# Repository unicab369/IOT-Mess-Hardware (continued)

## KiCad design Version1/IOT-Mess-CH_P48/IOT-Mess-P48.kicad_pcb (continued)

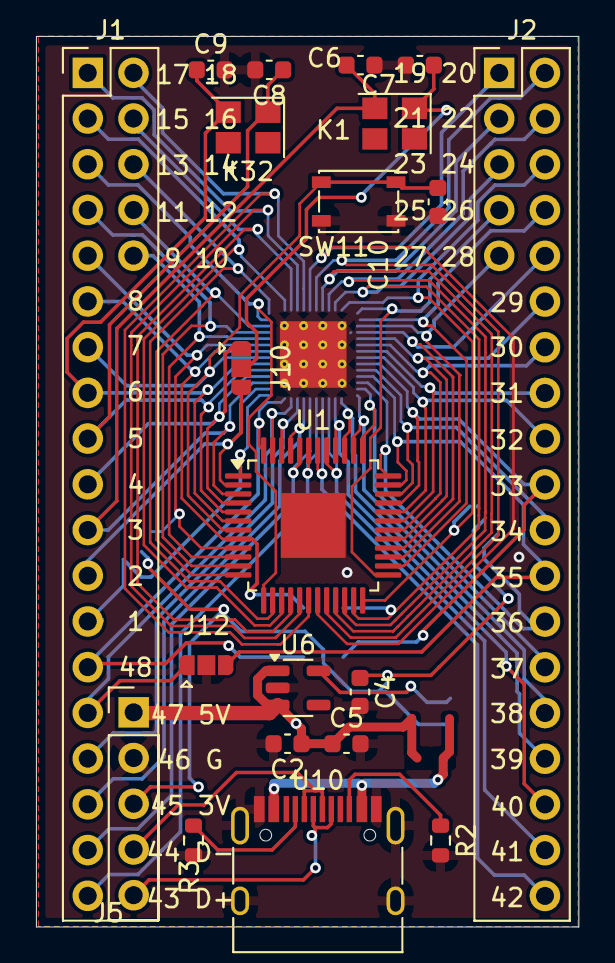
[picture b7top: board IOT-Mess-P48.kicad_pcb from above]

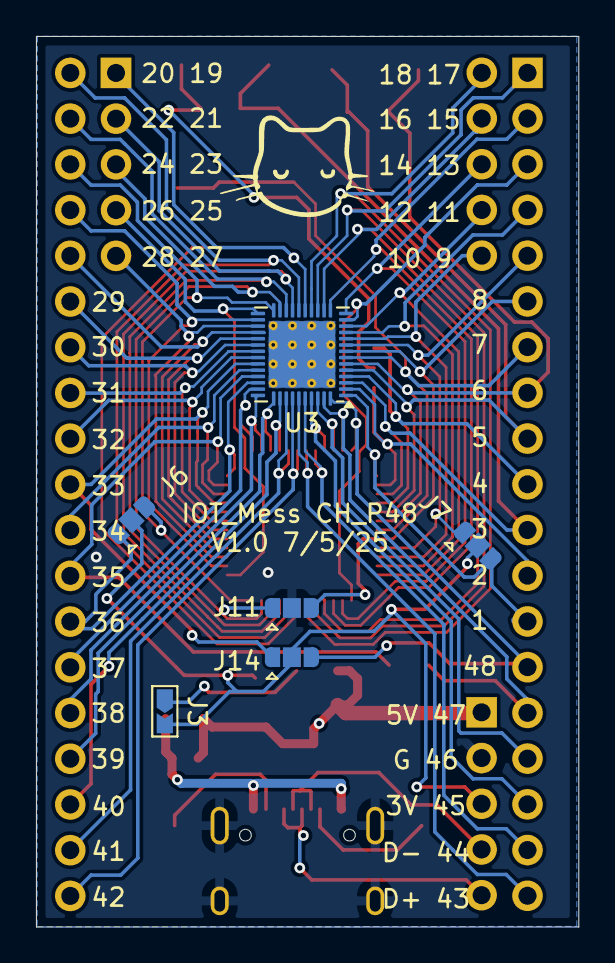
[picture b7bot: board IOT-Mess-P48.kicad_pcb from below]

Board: 2 copper layers, 30.1 x 49.5 mm, 27 parts (6 on the bottom side), 57 nets.

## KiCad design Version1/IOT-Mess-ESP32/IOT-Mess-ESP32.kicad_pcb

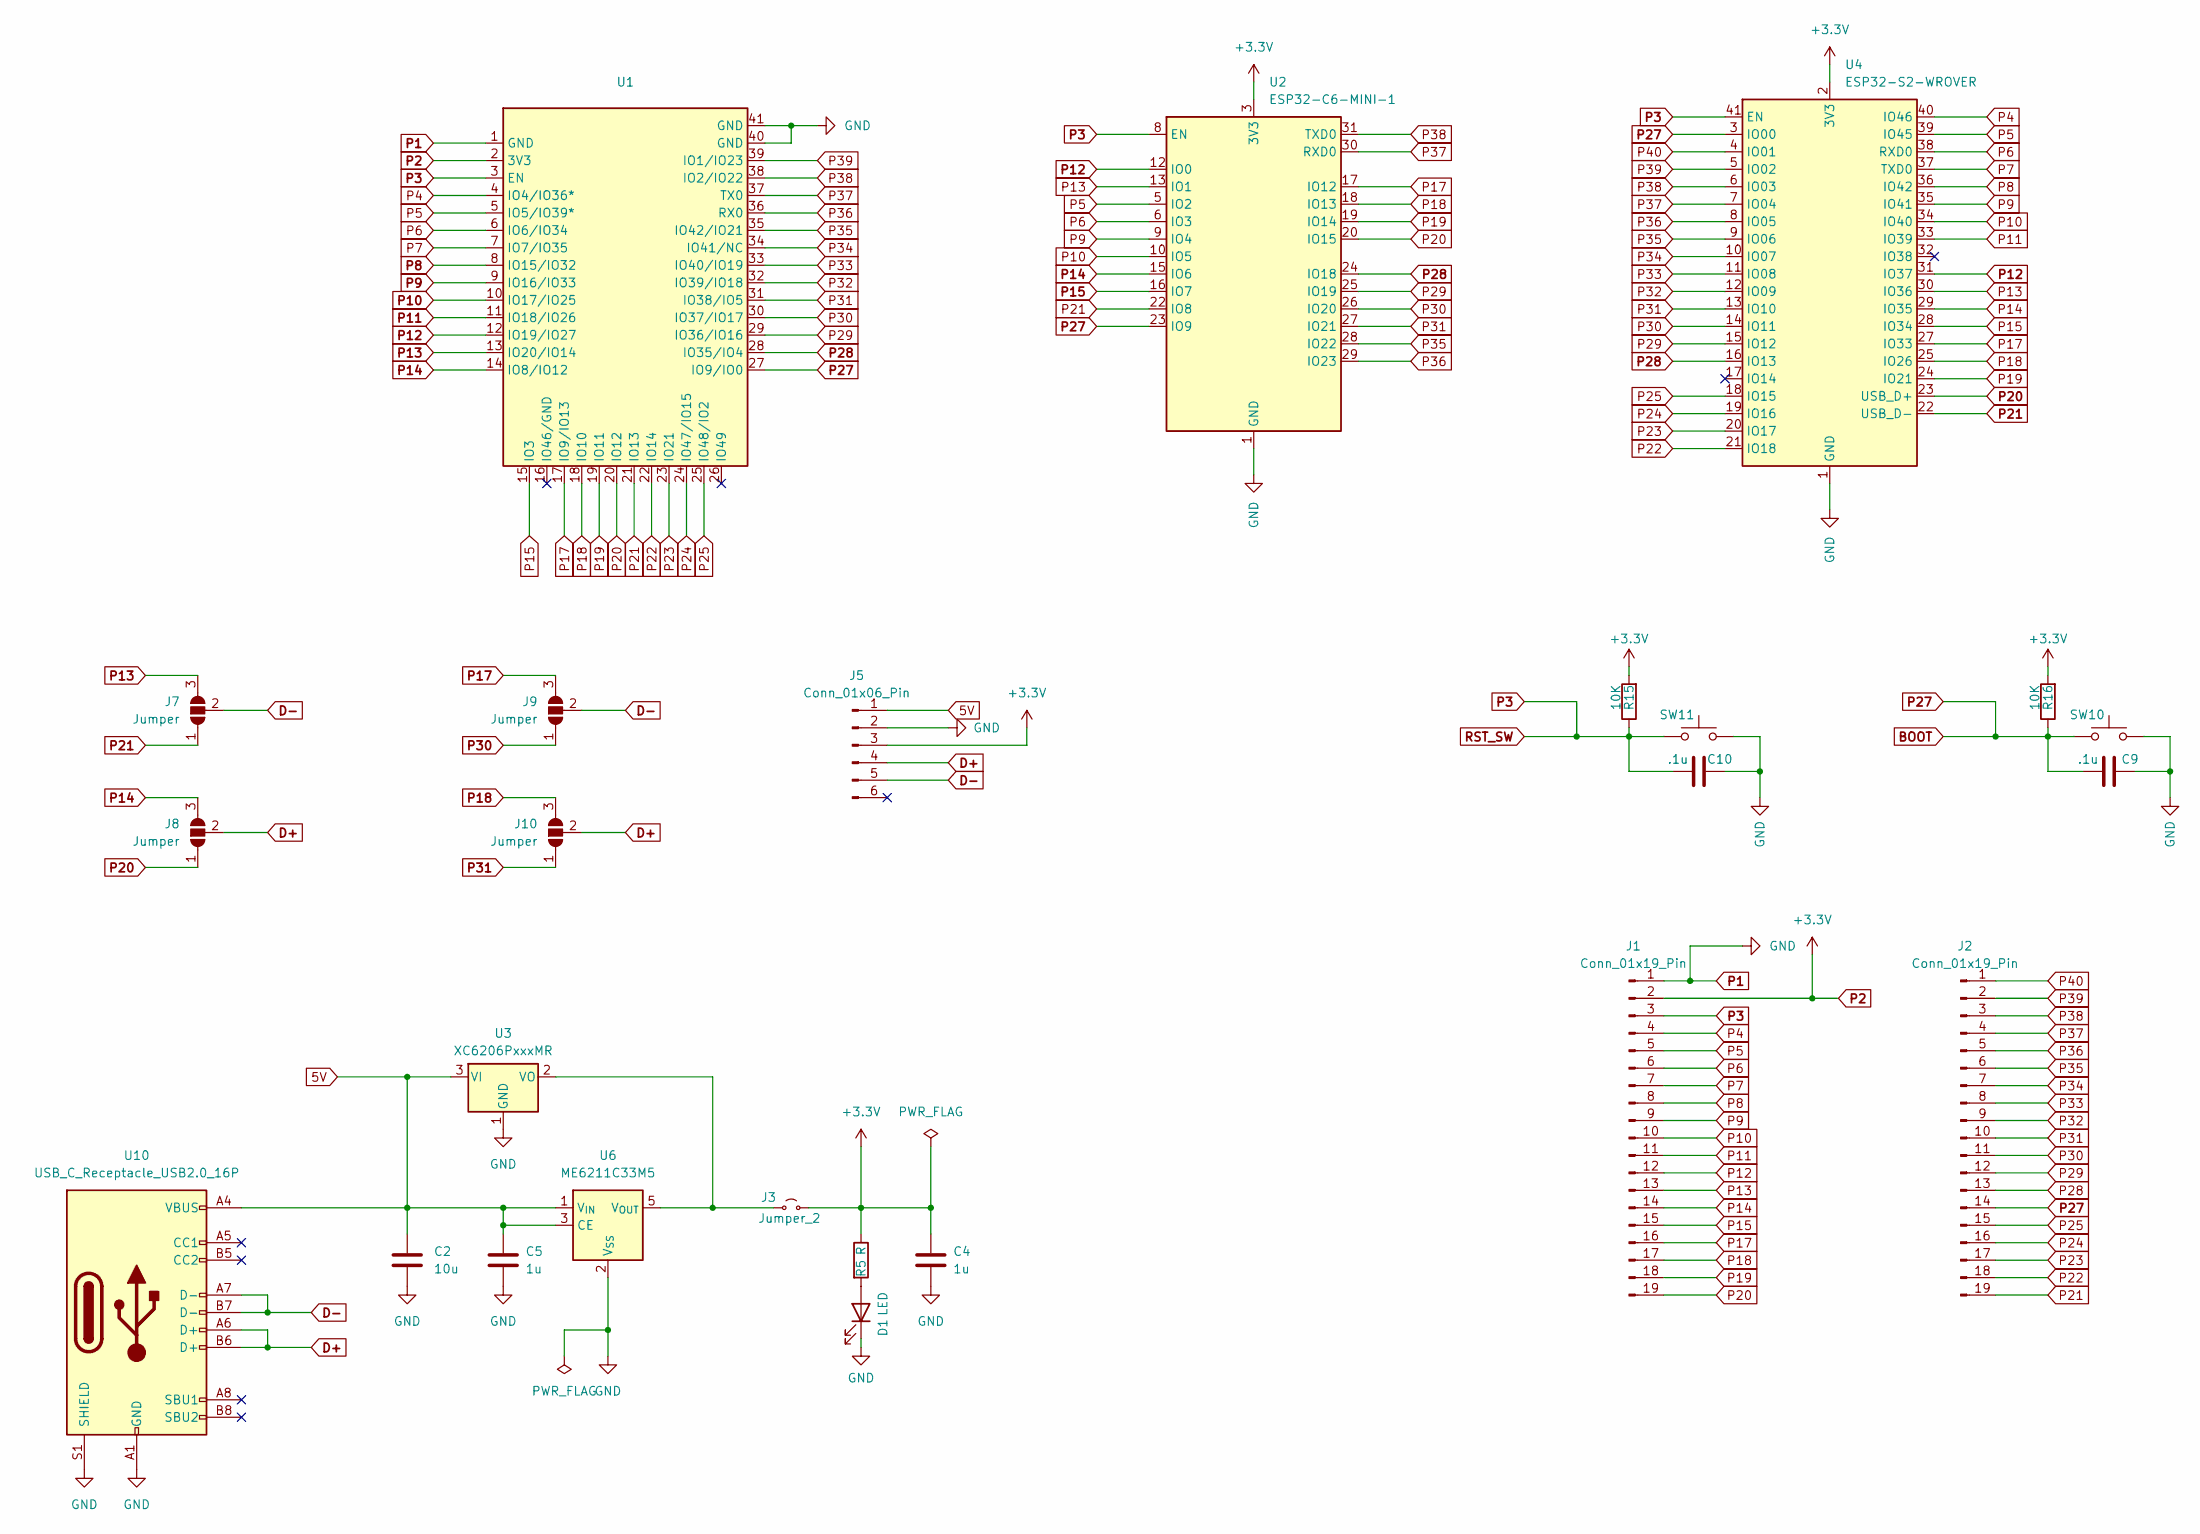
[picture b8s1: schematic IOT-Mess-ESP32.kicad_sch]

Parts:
C2: 10u; C_0603_1608Metric
C4, C5: 1u; C_0603_1608Metric
C9, C10: .1u; C_0603_1608Metric
D1: LED; LED_0603_1608Metric
J1, J2: Conn_01x19_Pin; PinHeader_1x19_P2.54mm_Vertical
J3: Jumper_2; Jumpper-triangle
J5: Conn_01x06_Pin; PinHeader_1x06_P2.54mm_Vertical
J7, J8, J9, J10: Jumper; Jumper-3_P1.3mm_Open_RoundedPad1.0x1.5mm
R5: R; R_0603_1608Metric
R15, R16: 10K; R_0603_1608Metric
SW10, SW11: SW_Push; SW_SPST_PTS810
U1: ESP32-S3-WROOM-1
U2: ESP32-C6-MINI-1
U3: XC6206PxxxMR; SOT-23-3
U4: ESP32-S2-WROVER
U6: ME6211C33M5; SOT-23-5
U10: USB_C_Receptacle_USB2.0_16P; USB_C_Receptacle_HRO_TYPE-C-31-M-12

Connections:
5V: C2.1, C5.1, J5.1, U3.3 (VI), U6.1 (V_{IN}), U6.3 (CE), U10.A4 (VBUS), U10.A9 (VBUS), U10.B4 (VBUS), U10.B9 (VBUS)
BOOT: C9.1, J2.14, R16.1, SW10.1, U1.27 (IO9/IO0), U2.23 (IO9), U4.3 (IO00)
D+: J5.4, J8.2 (C), J10.2 (C), U10.A6 (D+), U10.B6 (D+)
D-: J5.5, J7.2 (C), J9.2 (C), U10.A7 (D-), U10.B7 (D-)
unnamed: D1.2 (A), R5.2
unnamed: J3.1 (A), U3.2 (VO), U6.5 (V_{OUT})
P1: C2.2, C4.2, C5.2, C9.2, C10.2, D1.1 (K), J1.1, J5.2, SW10.2, SW11.2, U1.1 (GND), U1.40 (GND), U1.41 (GND), U2.1 (GND), U2.2 (GND), U2.11 (GND), U2.14 (GND), U2.36 (GND), U2.37 (GND), U2.38 (GND), U2.39 (GND), U2.40 (GND), U2.41 (GND), U2.42 (GND), U2.43 (GND), U2.44 (GND), U2.45 (GND), U2.46 (GND), U2.47 (GND), U2.48 (GND), U2.49 (GND), U2.50 (GND), U2.51 (GND), U2.52 (GND), U2.53 (GND), U3.1 (GND), U4.1 (GND), U4.26 (GND), U4.42 (GND), U4.43 (GND), U6.2 (V_{SS}), U10.A1 (GND), U10.A12 (GND), U10.B1 (GND), U10.B12 (GND), U10.S1 (SHIELD)
P2: C4.1, J1.2, J3.2 (B), J5.3, R5.1, R15.2, R16.2, U1.2 (3V3), U2.3 (3V3), U4.2 (3V3)
P3: C10.1, J1.3, R15.1, SW11.1, U1.3 (EN), U2.8 (EN), U4.41 (EN)
P4: J1.4, U1.4 (IO4/IO36*), U4.40 (IO46)
P5: J1.5, U1.5 (IO5/IO39*), U2.5 (IO2), U4.39 (IO45)
P6: J1.6, U1.6 (IO6/IO34), U2.6 (IO3), U4.38 (RXD0)
P7: J1.7, U1.7 (IO7/IO35), U4.37 (TXD0)
P8: J1.8, U1.8 (IO15/IO32), U4.36 (IO42)
P9: J1.9, U1.9 (IO16/IO33), U2.9 (IO4), U4.35 (IO41)
P10: J1.10, U1.10 (IO17/IO25), U2.10 (IO5), U4.34 (IO40)
P11: J1.11, U1.11 (IO18/IO26), U4.33 (IO39)
P12: J1.12, U1.12 (IO19/IO27), U2.12 (IO0), U4.31 (IO37)
P13: J1.13, J7.3 (B), U1.13 (IO20/IO14), U2.13 (IO1), U4.30 (IO36)
P14: J1.14, J8.3 (B), U1.14 (IO8/IO12), U2.15 (IO6), U4.29 (IO35)
P15: J1.15, U1.15 (IO3), U2.16 (IO7), U4.28 (IO34)
P17: J1.16, J9.3 (B), U1.17 (IO9/IO13), U2.17 (IO12), U4.27 (IO33)
P18: J1.17, J10.3 (B), U1.18 (IO10), U2.18 (IO13), U4.25 (IO26)
P19: J1.18, U1.19 (IO11), U2.19 (IO14), U4.24 (IO21)
P20: J1.19, J8.1 (A), U1.20 (IO12), U2.20 (IO15), U4.23 (USB_D+)
P21: J2.19, J7.1 (A), U1.21 (IO13), U2.22 (IO8), U4.22 (USB_D-)
P22: J2.18, U1.22 (IO14), U4.21 (IO18)
P23: J2.17, U1.23 (IO21), U4.20 (IO17)
P24: J2.16, U1.24 (IO47/IO15), U4.19 (IO16)
P25: J2.15, U1.25 (IO48/IO2), U4.18 (IO15)
P28: J2.13, U1.28 (IO35/IO4), U2.24 (IO18), U4.16 (IO13)
P29: J2.12, U1.29 (IO36/IO16), U2.25 (IO19), U4.15 (IO12)
P30: J2.11, J9.1 (A), U1.30 (IO37/IO17), U2.26 (IO20), U4.14 (IO11)
P31: J2.10, J10.1 (A), U1.31 (IO38/IO5), U2.27 (IO21), U4.13 (IO10)
P32: J2.9, U1.32 (IO39/IO18), U4.12 (IO09)
P33: J2.8, U1.33 (IO40/IO19), U4.11 (IO08)
P34: J2.7, U1.34 (IO41/NC), U4.10 (IO07)
P35: J2.6, U1.35 (IO42/IO21), U2.28 (IO22), U4.9 (IO06)
P36: J2.5, U1.36 (RX0), U2.29 (IO23), U4.8 (IO05)
P37: J2.4, U1.37 (TX0), U2.30 (RXD0), U4.7 (IO04)
P38: J2.3, U1.38 (IO2/IO22), U2.31 (TXD0), U4.6 (IO03)
P39: J2.2, U1.39 (IO1/IO23), U4.5 (IO02)
P40: J2.1, U4.4 (IO01)

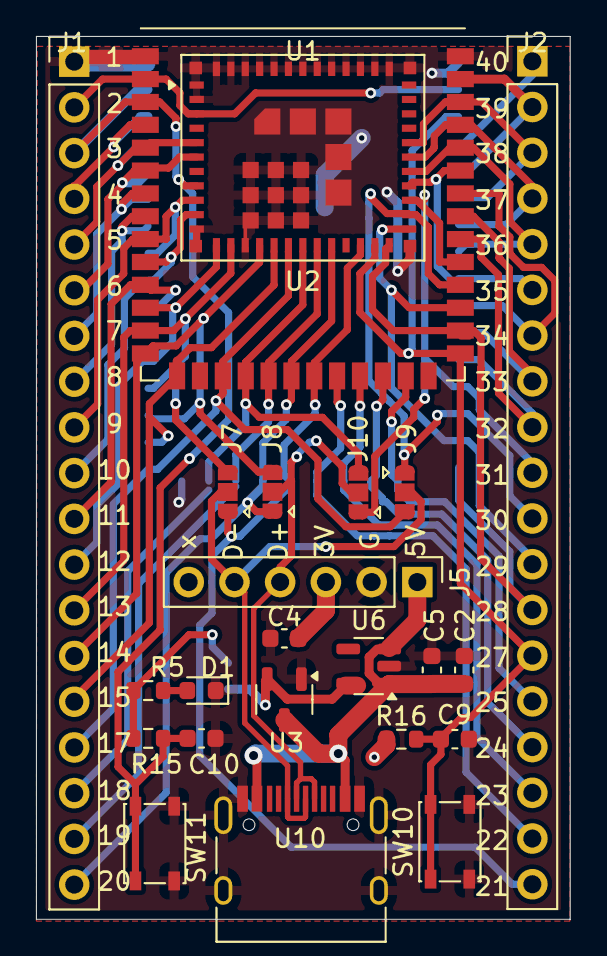
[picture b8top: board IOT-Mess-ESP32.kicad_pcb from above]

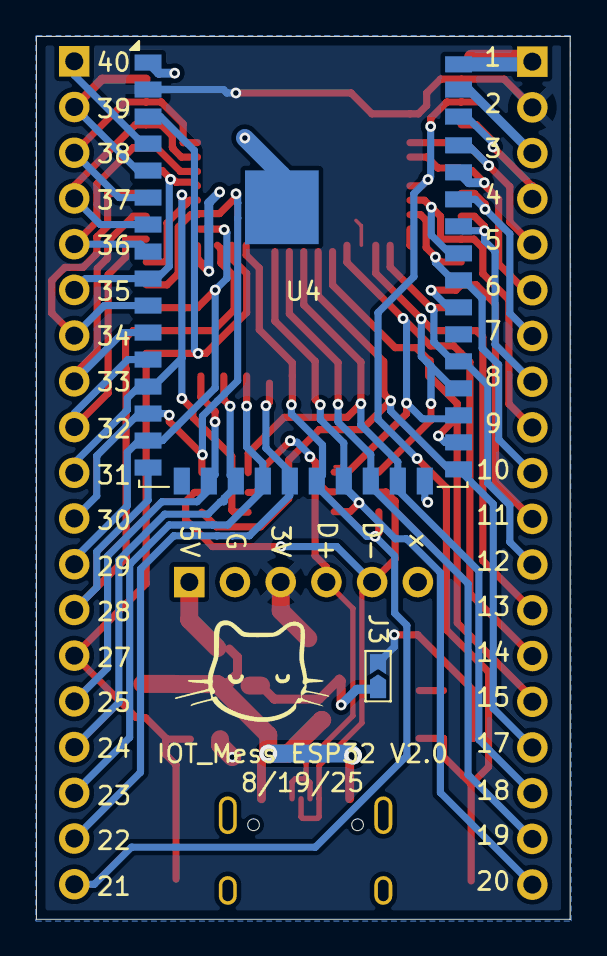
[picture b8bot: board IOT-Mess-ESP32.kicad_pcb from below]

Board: 2 copper layers, 29.6 x 49.0 mm, 25 parts (2 on the bottom side), 43 nets.
